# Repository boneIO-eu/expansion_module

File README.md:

# expansion_module
Expansion module for Relay Board

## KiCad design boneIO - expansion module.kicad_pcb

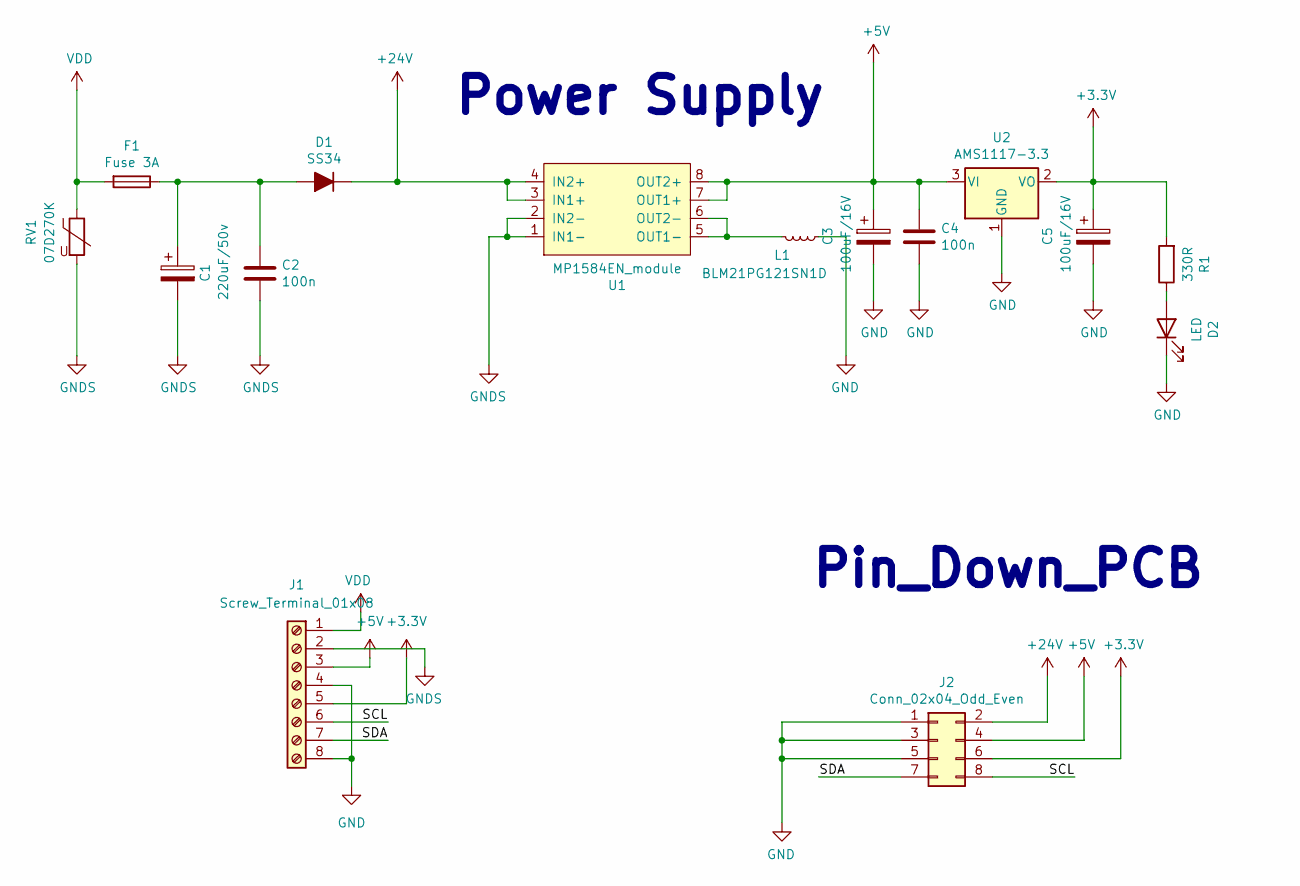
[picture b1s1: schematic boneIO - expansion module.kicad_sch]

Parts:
C1: 220uF/50v; CP_Elec_8x10
C2, C4: 100n; C_0603_1608Metric
C3, C5: 100uF/16V; CP_Elec_6.3x5.4; JLCPCB C72480
D1: SS34; D_SMA; JLCPCB C64982
D2: LED; C_0805_2012Metric
F1: Fuse 3A; Fuse_2512_6332Metric
J1: Screw_Terminal_01x08; PhoenixContact_MSTBA_2,5_8-G_1x08_P5.00mm_Horizontal
J2: Conn_02x04_Odd_Even; PinHeader_2x04_P2.54mm_Vertical
L1: BLM21PG121SN1D; L_0805_2012Metric
R1: 330R; R_0603_1608Metric
RV1: 07D270K; RV_Disc_D7mm_W3.5mm_P5mm; JLCPCB C317745
U1: MP1584EN_module; MP1584-_module
U2: AMS1117-3.3; SOT-223-3_TabPin2

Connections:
+3V3: C5.1, J1.5, J2.6, R1.2, U2.2 (VO)
+5V: C3.1, C4.1, J1.3, J2.4, U1.7 (OUT1+), U1.8 (OUT2+), U2.3 (VI)
+24V: D1.1 (K), J2.2, U1.3 (IN1+), U1.4 (IN2+)
/SCL: J1.6, J2.8
/SDA: J1.7, J2.7
GND: C3.2, C4.2, C5.2, D2.1 (K), J1.4, J1.8, J2.1, J2.3, J2.5, L1.2, U2.1 (GND)
GNDS: C1.2, C2.2, J1.2, RV1.2, U1.1 (IN1-), U1.2 (IN2-)
unnamed: C1.1, C2.1, D1.2 (A), F1.1
unnamed: D2.2 (A), R1.1
unnamed: L1.1, U1.5 (OUT1-), U1.6 (OUT2-)
VDD: F1.2, J1.1, RV1.1

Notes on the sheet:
Pin_Down_PCB
Power Supply

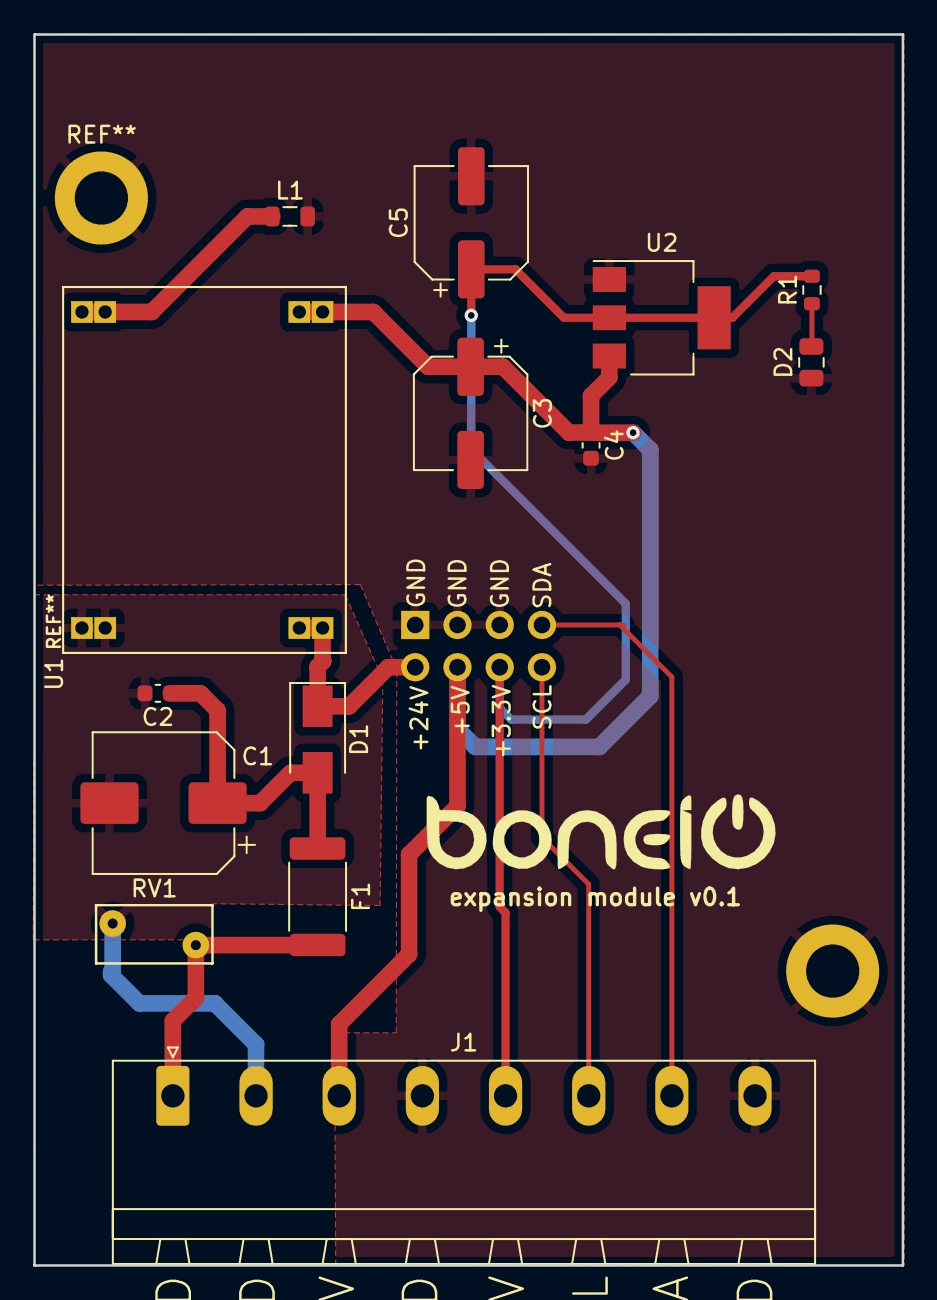
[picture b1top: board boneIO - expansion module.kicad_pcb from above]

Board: 2 copper layers, 52.2 x 74.0 mm, 15 parts (1 on the bottom side), 11 nets.

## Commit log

2022-02-24 expansion module v0.1
